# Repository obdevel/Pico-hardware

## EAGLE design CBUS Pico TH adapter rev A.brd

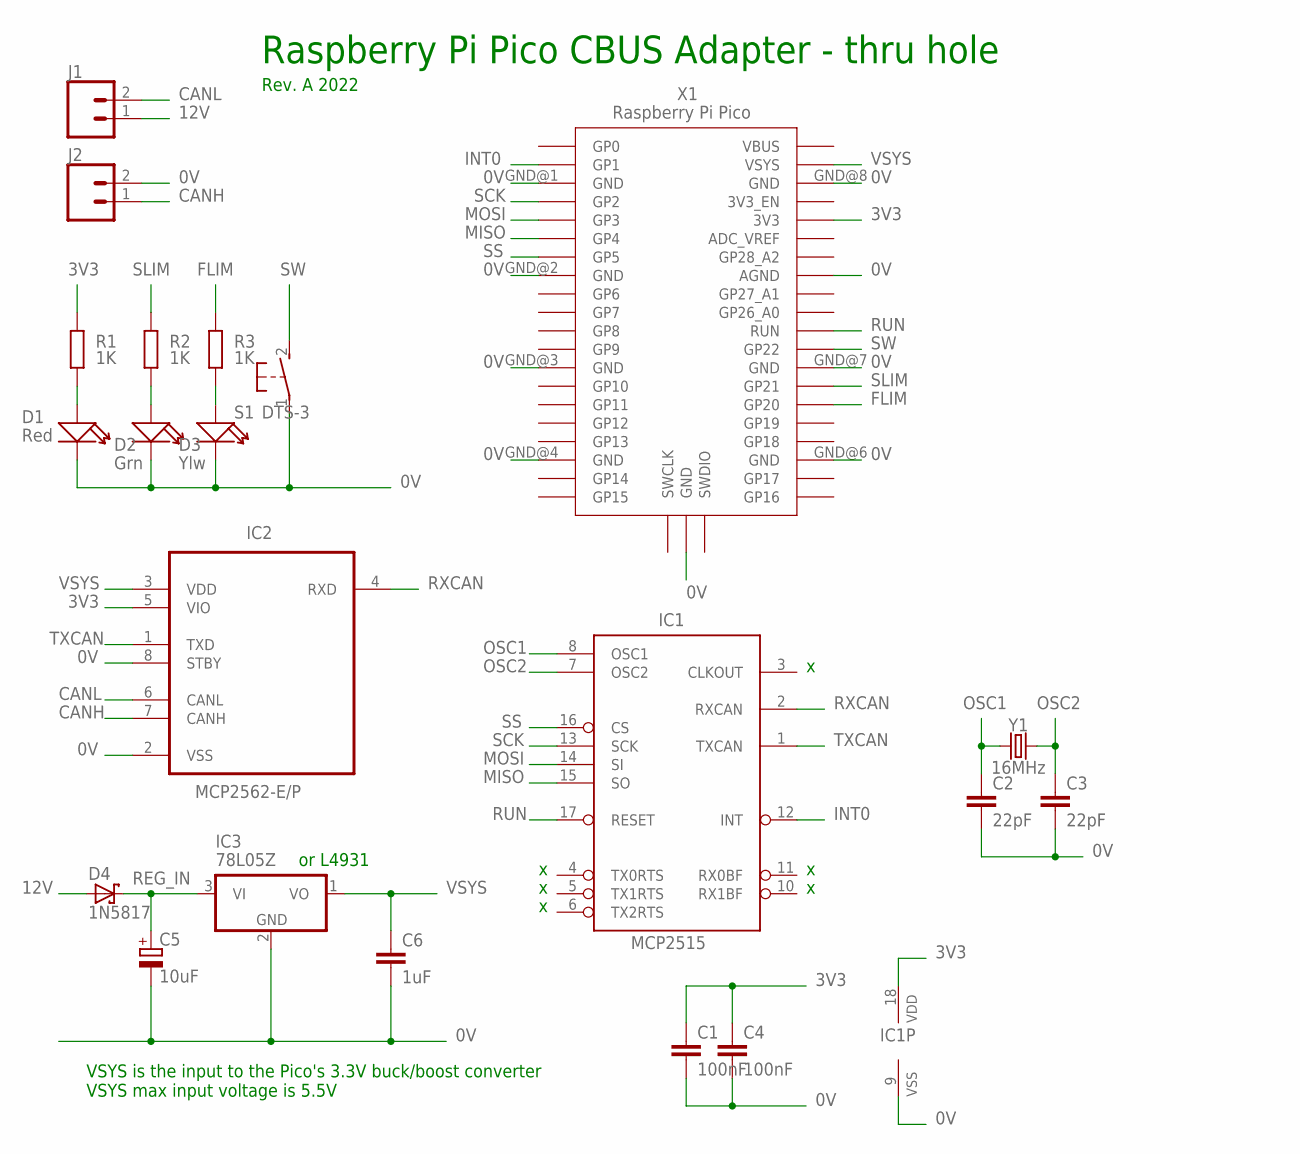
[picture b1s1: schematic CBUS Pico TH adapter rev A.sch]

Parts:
C1, C4: 100nF; C025-025X050
C2, C3: 22pF; C025-025X050
C5: 10uF; E2-4
C6: 1uF; C025-025X050
D1: Red; LED2-2.54-D3.0MM
D2: Grn; LED2-2.54-D3.0MM
D3: Ylw; LED2-2.54-D3.0MM
D4: 1N5817; DO41-10
IC1: MCP2515; DIP18
IC2: MCP2562-E/P; DIP254P762X533-8
IC3: 78L05Z; TO92
J1, J2: CONN_023.5MM; SCREWTERMINAL-3.5MM-2
R1, R2, R3: 1K; 0207/10
S1: DTS-3
X1: Raspberry Pi Pico; RPI_PICO_TH
Y1: 16MHz; HC49US

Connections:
0V: C1.2, C2.2, C3.2, C4.2, C5.-, C6.2, D1.K (-), D2.K (-), D3.K (-), IC1.9 (VSS), IC2.2 (VSS), IC2.8 (STBY), IC3.2 (GND), J2.2, S1.1, X1.AGND, X1.GND@1 (GND), X1.GND@2 (GND), X1.GND@3 (GND), X1.GND@4 (GND), X1.GND@5 (GND), X1.GND@6 (GND), X1.GND@7 (GND), X1.GND@8 (GND)
3V3: C1.1, C4.1, IC1.18 (VDD), IC2.5 (VIO), R1.1, X1.3V3
12V: D4.A, J1.1
CANH: IC2.7 (CANH), J2.1
CANL: IC2.6 (CANL), J1.2
FLIM: R3.1, X1.GP20
INT0: IC1.12 (INT), X1.GP1
MISO: IC1.15 (SO), X1.GP4
MOSI: IC1.14 (SI), X1.GP3
unnamed: D1.A (+), R1.2
unnamed: D2.A (+), R2.2
unnamed: D3.A (+), R3.2
OSC1: C2.1, IC1.8 (OSC1), Y1.1
OSC2: C3.1, IC1.7 (OSC2), Y1.2
REG_IN: C5.+, D4.C, IC3.3 (VI)
RUN: IC1.17 (RESET), X1.RUN
RXCAN: IC1.2 (RXCAN), IC2.4 (RXD)
SCK: IC1.13 (SCK), X1.GP2
SLIM: R2.1, X1.GP21
SS: IC1.16 (CS), X1.GP5
SW: S1.2, X1.GP22
TXCAN: IC1.1 (TXCAN), IC2.1 (TXD)
VSYS: C6.1, IC2.3 (VDD), IC3.1 (VO), X1.VSYS

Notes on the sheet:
Raspberry Pi Pico CBUS Adapter - thru hole
Rev. A 2022
VSYS is the input to the Pico's 3.3V buck/boost converter VSYS max input voltage is 5.5V
or L4931

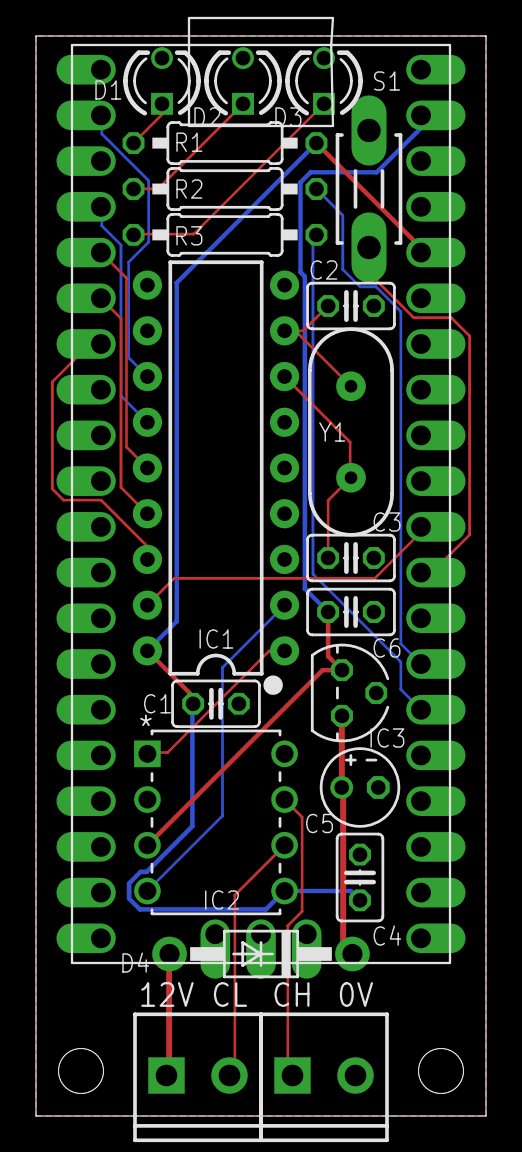
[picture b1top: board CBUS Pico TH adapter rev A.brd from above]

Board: 2 copper layers, 25.0 x 60.0 mm, 21 parts (0 on the bottom side), 23 nets.

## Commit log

2023-01-14 Initial creation
2023-01-21 Doc changes

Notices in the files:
parts and their libraries:
SparkFun-IC-Comms: Licensing: Creative Commons ShareAlike 4.0 International - https://creativecommons.org/licenses/by-sa/4.0
